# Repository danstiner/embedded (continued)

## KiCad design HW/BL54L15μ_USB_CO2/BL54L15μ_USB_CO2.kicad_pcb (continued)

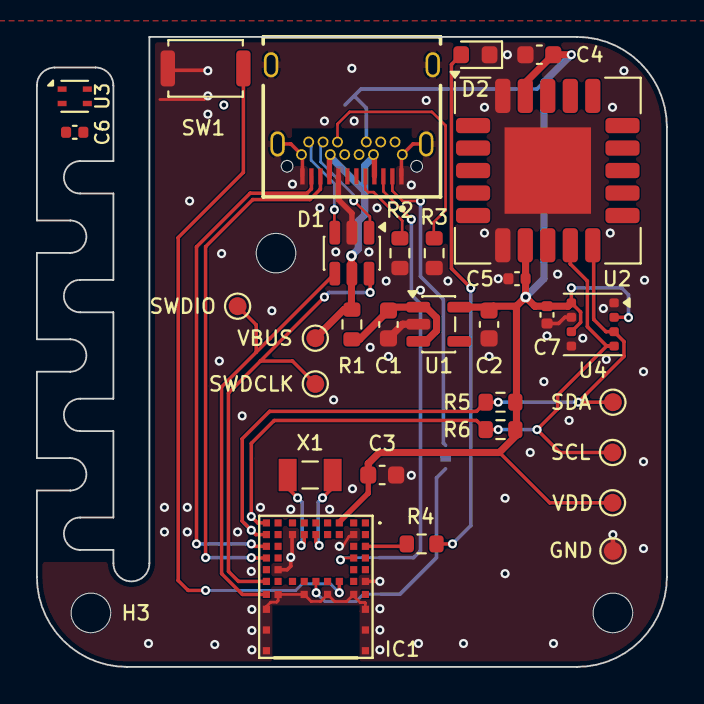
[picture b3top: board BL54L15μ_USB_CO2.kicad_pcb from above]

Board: 2 copper layers, 35.0 x 35.0 mm, 34 parts (1 on the bottom side), 22 nets.

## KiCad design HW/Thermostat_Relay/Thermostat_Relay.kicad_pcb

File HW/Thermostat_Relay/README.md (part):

# Thermostat relay board

## 1. Scope

Control board for two 24 VAC HVAC relays that can be driven by ESP32 GPIO pins. Compatible with
any typical single-stage gas furnace. Heat pumps are out of scope, they require additional
relay channels. Powering the ESP32 is also out of scope.

## 2. Background

Furnaces take mains power and step it down to 24 VAC. This is supplied on the R wire to a thermostat,
which can close the circuit with the W return wire to call for heat. In a modern furnace this is an
input to a digital control board and only draws a few milliamps. In older furnaces this directly
drives a relay coil and can draw an ampere or more of current.

## 3. Requirements

| ID   | Requirement                                                                                 |
| ---- | ------------------------------------------------------------------------------------------- |
| R-1  | Switch two independent circuits, R–W and R–G, each from one 3.3 V GPIO; high = closed       |
| R-2  | A circuit is open when its input is low or floating, or the MCU is off, in reset or booting |
| R-3  | Carry 1 A RMS continuously per circuit at 50 °C, and switch loads as small as 1 mA          |
| R-4  | Withstand 45 V peak (Class 2 transformer limit: 30 V RMS open-circuit, 42.4 V peak)         |
| R-5  | Survive switching off a 1 A inductive load                                                  |
| R-6  | Leak less than 100 µA through an open circuit                                               |
| R-7  | Galvanically isolate the MCU from the 24 VAC side                                           |
| R-8  | Draw no more than 10 mA per closed circuit from the MCU                                     |
| R-9  | Interrupt a short on the field wiring without damage to the wiring                          |
| R-10 | Surface-mount parts that can be reflowed on a hot plate; through-hole connectors            |

Notes
- 1 A is the load current TI's 24 VAC thermostat relay reference design (TIDA-010085) is
  specified for, and more than half of what a 40 VA Class 2 transformer can supply (1.7 A)
- 50 °C is a conservative ambient
- 30 V RMS maximum for thermostat circuits follows from them being Class 2 under UL 5085-3

## 4. Design trades

### 4.1 24 VAC switch

|                          | Relay    | **PhotoMOS** | Driver + FETs | TPSI8830    | TRIAC       |
| ------------------------ | -------- | ------------ | ------------- | ----------- | ----------- |
| Hold current (R-8)       | 70–90 mA | 5–10 mA      | ~5 mA         | ~5 mA       | ~10 mA      |
| 1 mA load (R-3)          | marginal | ✓            | ✓             | ✓           | ✗           |
| Leakage (R-6)            | ✓        | ✓            | ✓             | ✓           | ✗ (snubber) |
| Parts per channel        | 4        | 4            | ~10           | 3–4         | 5+          |
| Available to buy         | ✓        | ✓            | ✓             | ✗ (preview) | ✓           |
| Short-circuit protection | rugged   | none         | possible      | built in    | none        |

**Chosen: PhotoMOS.** An LED inside the package lights a photovoltaic cell that turns on two
back-to-back MOSFETs. It meets every requirement with only four parts per channel, making it easy
to use for bringing up a v1 board. A separate fuse is added for short-circuit protection.
Downsides of PhotoMOS are slightly higher cost and LED aging.

TI's reference designs for 24 VAC thermostat switching (section 10) both use discrete MOSFET pairs
with a separate isolated gate drive. This is likely a lower cost design at scale production,
using either small transformers or capacitive isolation instead of optocouplers. It also enables
microsecond switching for power-stealing, adding current-sensing circuitry, and the ability
to share one isolated supply across all channels. None of these are relevant to a v1 prototype.

TI's upcoming TPSI8830 is worth watching: it integrates a capacitively isolated driver with
back-to-back MOSFETs and overcurrent protection into a single package with 30 mΩ on resistance.

### 4.2 Furnace terminal block

Thermostat wire is nominally 18 AWG solid, connected to either screw terminals or screwless
spring terminals.

|                    | **2601-1103**        | 805-303             | 2060-453             | MKDS 1,5/3-5,08     |
| ------------------ | -------------------- | ------------------- | -------------------- | ------------------- |
| Release            | lever                | push-button         | small push-button    | screw               |
| Solid wire         | 26–14 AWG            | 24–16 AWG           | 24–18 AWG            | 26–14 AWG           |
| Pitch              | 3.5 mm               | 3.5 mm              | 4 mm                 | 5.08 mm             |
| Width × depth      | 13.0 × 15.7 mm       | 12.0 × 13.6 mm      | 11.9 × 13.1 mm       | 15.2 × 9.8 mm       |
| Height above board | about 16 mm          | 10.5 mm             | 4.5 mm               | 13.8 mm             |
| Mounting           | THT, 2 pins per pole | THT, 1 pin per pole | SMD, 2 pads per pole | THT, 1 pin per pole |

**Chosen: 2601-1103.** For prototyping we choose screwless spring terminals. Solid wire can be
pushed in by hand, and released by hand with a small lever. The 805-303 is a close alternative.
The 2060-453 has a lower profile, but release is a small button that may require a tool, and
18 AWG is the top of its range. Screw terminals have a wider pitch and require a screwdriver,
but they are typically cheaper if that becomes a driving concern.

## 5. Circuit

Two channels share the R input, each with its own fuse. Only the heat channel is shown. The
fan channel is the same except that its fuse is on pin 6 of the switch and G on pin 4; the
switch is symmetric, so this only simplifies the layout.

```
 logic side (3.3 V, USB ground) :        furnace side (24 VAC, floating)
                                :
 W_EN    o--+--[R1 220Ω]---+    :    +------+------------- o W
            |            1 | U1 :    | 6    |
         [R2 10k]        [LED]~~:~~[FETs]  [D1 TVS]
            |            2 |    :    | 4    |
 GND     o--+--------------+    :    +------+---[F1 2A]--- o R
```

### 5.1 Switch: Toshiba TLP3109A (U1)

| Datasheet value                 |                               | Requirement     |
| ------------------------------- | ----------------------------- | --------------- |
| Off-state voltage               | 100 V max                     | 45 V peak (R-4) |
| On-state current, AC connection | 3 A at 25 °C, 2.25 A at 50 °C | 1 A (R-3)       |
| On-resistance                   | 50 mΩ typ, 65 mΩ max          | –               |
| LED trigger current             | 3 mA max                      | see 5.2         |
| Off-state leakage, capacitance  | 1 µA max, 460 pF              | see 5.7         |
| Isolation                       | 1500 V RMS                    | galvanic (R-7)  |
| Pulse current                   | 9 A for 100 ms                | see 5.6         |

- Pins 4 and 6 (the two drains) are the switch; pin 5 (common source) is left open. That
  puts the two MOSFETs in series back to back, which is what lets the part block and
  conduct both polarities of AC.
- Heat: at 1 A and the maximum 65 mΩ the switch generates about 0.07 W of heat
- 100 V off-state max was chosen to have margin to clamp surges over the expected 42.4 V peak
  Class 2 transformer output, similar to TI reference design TIDA-010085.

Parts considered (DigiKey, 2026-11-12, quantity 1):

| Part         | Rating       | At 50 °C | R_on max | Isolation | Price           | Outcome     |
| ------------ | ------------ | -------- | -------- | --------- | --------------- | ----------- |
| **TLP3109A** | 100 V, 3 A   | 2.25 A   | 65 mΩ    | 1500 V    | $4.14, in stock | chosen      |
| TLP3546A     | 100 V, 3.5 A | 2.6 A    | 80 mΩ    | 2500 V    | $4.11, no stock | unavailable |

### 5.2 LED resistor: 220 Ω (R1)

The TLP3109A datasheet recommends 5 to 25 mA. `I = (V_GPIO − V_LED) / R`:

| Case            | V_GPIO | V_LED  | I      |
| --------------- | ------ | ------ | ------ |
| Worst-case low  | 3.0 V  | 1.80 V | 5.4 mA |
| Nominal         | 3.3 V  | 1.65 V | 7.5 mA |
| Worst-case high | 3.47 V | 1.50 V | 9.0 mA |

### 5.3 Optional pull-down: 10 kΩ (R2)

Optional pull-down to hold the LED input at ~0 V when not being driven (R-2). Overrides the
pull-up glitch during boot that some ESP32 pins exhibit. Optional because the TLP3109A is
guaranteed off below 0.1 mA of LED current, and a 45 kΩ pull-up supplies only about 0.05 mA.
Cannot override a pin that actively drives high during boot, those high-level glitch pins
should be avoided.

### 5.4 Optional indicator: 4.7 kΩ and a red LED

One LED per channel, from the control input to ground, lit while the ESP32 commands the
channel closed. At 4.7 kΩ it draws about 0.3 mA, 0.4 mA worst case. With the pull-down and
indicator both fitted, a closed channel draws at most 9.0 + 0.35 + 0.4 = 9.7 mA (R-8).

### 5.5 Clamp: Bidirectional TVS (D1)

When the switch opens on a relay coil or gas valve, the coil's inductance creates a voltage
spike across the switch. A bidirectional TVS across the switch limits that voltage (R-5)
to prevent damage to the switch.

|                     | SMBJ48CA       | Requirement                       |
| ------------------- | -------------- | --------------------------------- |
| Reverse stand off   | 48 V           | ≥ 45 V peak (R-4)                 |
| Max clamp           | 77.4 V @ 7.8 A | ≤ 80 V (switch's recommended max) |
| Max reverse leakage | 1 µA           | < 100 µA total leakage (R-6)      |

An RC snubber is ruled out by R-6: a typical 100 nF passes about 1.1 mA at 60 Hz with the
switch open, which could trigger a phantom call for heat on a modern furnace control board.

### 5.6 Fuses: 2 A very fast-acting, one per channel (F1)

Each fuse opens if its circuit is shorted while that channel is closed (R-9): a
shorted relay coil, or the wire touching the transformer's return or grounded metal. That
protects the cable, the transformer and, for moderate fault currents, the switch. One fuse
per channel means a fault on the fan wire cannot take out the heat, and each fuse is sized
for one load, not the sum.

| Littelfuse 0466002.NR | Datasheet                            | Requirement                       |
| --------------------- | ------------------------------------ | --------------------------------- |
| Voltage rating        | 63 VAC                               | 30 V RMS (R-4)                    |
| Interrupting rating   | 50 A at 63 VAC                       | transformer short-circuit current |
| Continuous current    | 1.5 A at 25 °C, about 1.3 A at 50 °C | 1 A (R-3)                         |
| Opens at 200 % (4 A)  | within 5 s                           | –                                 |
| Opens at 300 % (6 A)  | within 0.2 s                         | –                                 |
| Melting I²t           | 0.23 A²s                             | below the switch's 8 A²s          |
| Cold resistance       | 30 mΩ                                | –                                 |

- Sizing: Littelfuse's guidance is to run a fuse at no more than 75 % of its rating at
  25 °C, which gives 1.5 A. The datasheet rerates a further 20 % at 70 °C; interpolating,
  about 11 % at 50 °C gives 1.3 A. That leaves about 30 % margin over a 1 A load. Relay
  coil inrush against the low melting I²t is unverified (section 9).
- Compared with others: TI recommends the same 2 A fast fuse for its 1 A design
  (TIDA-010085) and tested with the 1.5 A part of this series. Furnace control boards
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
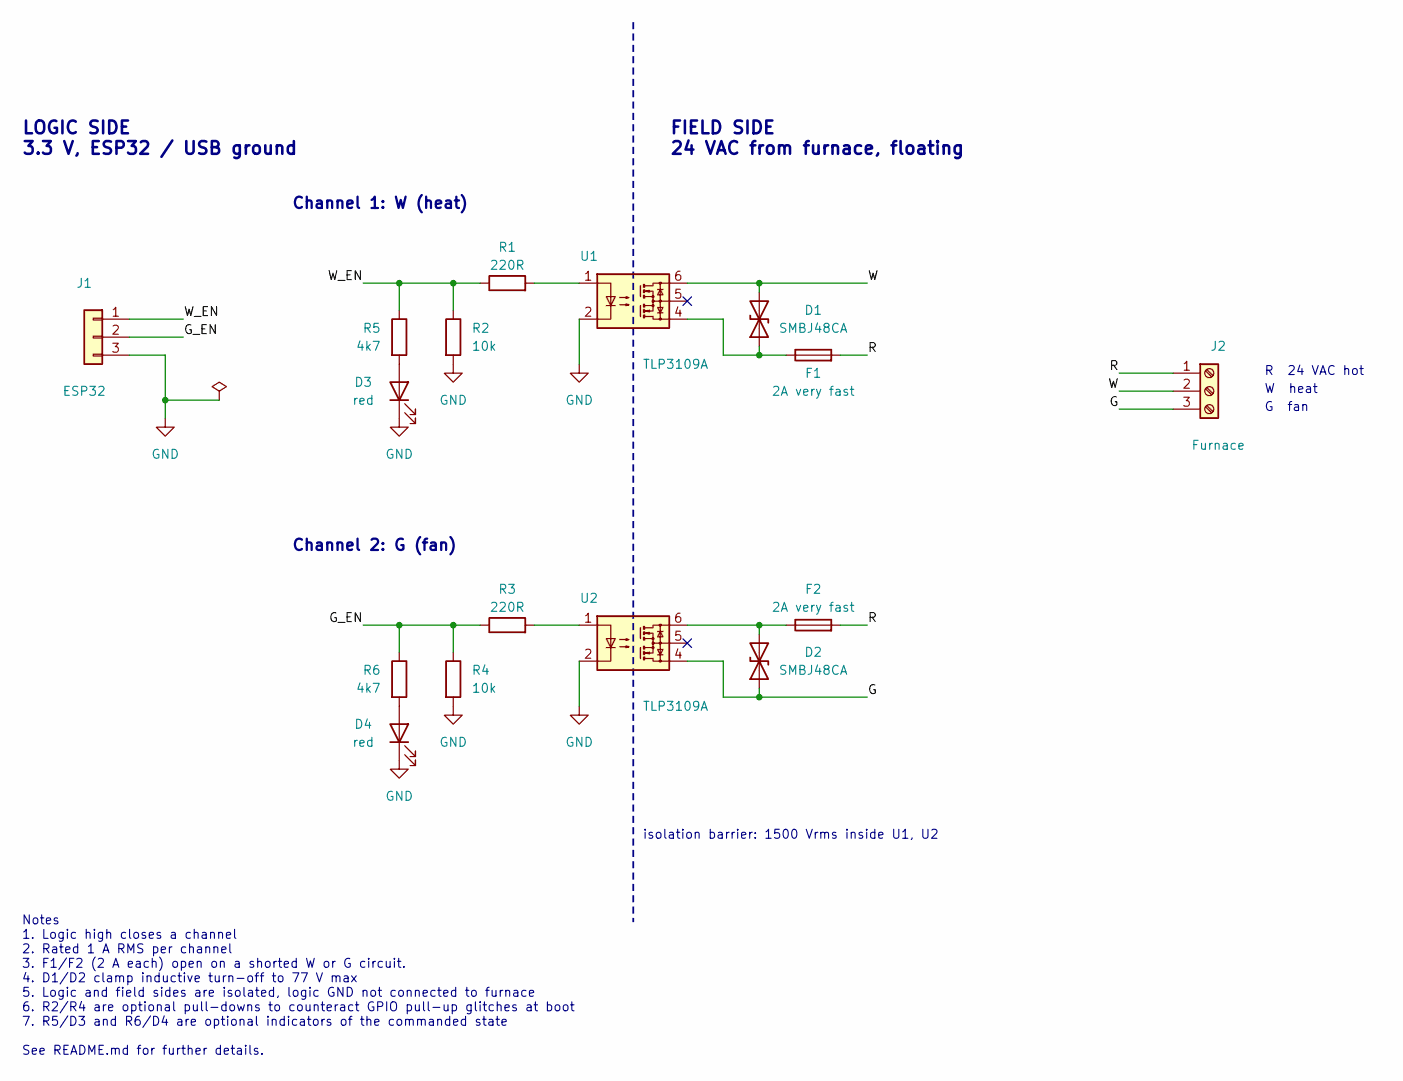
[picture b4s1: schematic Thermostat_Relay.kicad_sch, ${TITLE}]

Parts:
D1, D2: SMBJ48CA; D_SMB_Handsoldering; MPN SMBJ48CA
D3, D4: red; LED_0603_1608Metric_Pad1.05x0.95mm_HandSolder; MPN 150060SS75000
F1, F2: 2A very fast; Fuse_1206_3216Metric_Pad1.42x1.75mm_HandSolder; MPN 0466002.NR
J1: ESP32; PinHeader_1x03_P2.54mm_Vertical
J2: Furnace; TerminalBlock_WAGO_2601-1103_1x03_P3.50mm_Horizontal; MPN 2601-1103
R1, R3: 220R; R_0603_1608Metric_Pad0.98x0.95mm_HandSolder; Tolerance 1%; MPN RC0603FR-07220RL
R2, R4: 10k; R_0603_1608Metric_Pad0.98x0.95mm_HandSolder; MPN RC0603FR-0710KL
R5, R6: 4k7; R_0603_1608Metric_Pad0.98x0.95mm_HandSolder; MPN RC0603FR-074K7L
U1, U2: TLP3109A; 2p54SOP6_TOS-M; MPN TLP3109A(TP,F

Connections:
/G: D2.1 (A1), J2.3, U2.4
/G_EN: J1.2, R3.1, R4.1, R6.1
/R: F1.2, F2.2, J2.1
/W: D1.2 (A2), J2.2, U1.6
/W_EN: J1.1, R1.1, R2.1, R5.1
GND: D3.1 (K), D4.1 (K), J1.3, R2.2, R4.2, U1.2, U2.2
unnamed: D1.1 (A1), F1.1, U1.4
unnamed: D2.2 (A2), F2.1, U2.6
unnamed: D3.2 (A), R5.2
unnamed: D4.2 (A), R6.2
unnamed: R1.2, U1.1
unnamed: R3.2, U2.1

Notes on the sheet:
FIELD SIDE 24 VAC from furnace, floating
R 24 VAC hot
LOGIC SIDE 3.3 V, ESP32 / USB ground
Channel 2: G (fan)
W heat
Channel 1: W (heat)
Notes 1. Logic high closes a channel 2. Rated 1 A RMS per channel 3. F1/F2 (2 A each) open on a shorted W or G circuit. 4. D1/D2 clamp inductive turn-off to 77 V max 5. Logic and field sides are isolated, logic GND not connected to furnace 6. R2/R4 are optional pull-downs to counteract GPIO pull-up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
G fan
isolation barrier: 1500 Vrms inside U1, U2

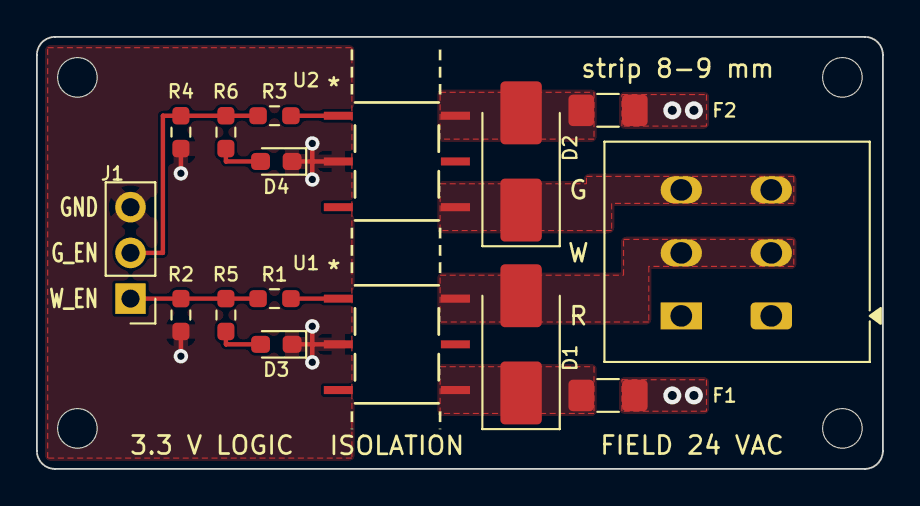
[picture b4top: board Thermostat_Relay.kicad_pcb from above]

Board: 2 copper layers, 47.0 x 24.0 mm, 20 parts (0 on the bottom side), 12 nets.

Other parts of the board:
H1, H2, H3, H4: MountingHole_2.2mm_M2

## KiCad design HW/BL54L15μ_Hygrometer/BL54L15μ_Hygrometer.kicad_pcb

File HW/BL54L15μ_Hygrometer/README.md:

+-----------+-----+----------------------+-----------------------------------------+--------------------------------------------------------------------------------------+
| Reference | Qty | Value                | Part Number                             | Footprint                                                                            |
+-----------+-----+----------------------+-----------------------------------------+--------------------------------------------------------------------------------------+
| BT1       | 1   | CR2 Battery          | 1011                                    | 1011:BAT_1011                                                                        |
| BZ1       | 1   | AST0827MW-03BTRQ     | AST0827MW-03BTRQ                        | AST0827MW-03BTRQ:AST0827MW-03BTRQ_MAL                                                |
| C1        | 1   | 100nF                | GRM155R61A104KA01J                      | Capacitor_SMD:C_0402_1005Metric                                                      |
| C2,C3     | 2   | 10μF                 | CL10A106KP8NNNC                         | Capacitor_SMD:C_0603_1608Metric                                                      |
| D1,D2     | 2   | 5V TVS               | TPD1E10B06DPYR                          | Diode_SMD:D_0402_1005Metric                                                          |
| D3        | 1   | MBR0520L             | MBR0520LT3G                             | Diode_SMD:D_SOD-123                                                                  |
| IC1       | 1   | nrf54L 453-00223R    | 453-00223R                              | 453-00223R:45300223R                                                                 |
| J1        | 1   | Conn_ARM_JTAG_SWD_10 | 3220-10-0300-00                         | Connector_PinHeader_1.27mm:PinHeader_2x05_P1.27mm_Vertical_SMD                       |
| P1,P2     | 2   | 6mmMetalDome         | Triangle 6mm - 0.8mm feet               | MetalDomeSwitch:TriangleDome_Diameter6mm                                             |
| Q1        | 1   | AOSS32136C           | AOSS32136C                              | Package_TO_SOT_SMD:SOT-23-3                                                          |
| R1,R2     | 2   | 10kΩ                 | RC0402FR-0710KL                         | Resistor_SMD:R_0402_1005Metric                                                       |
| R3,R7     | 2   | 1MΩ                  | RC0402FR-071ML                          | Resistor_SMD:R_0402_1005Metric                                                       |
| U1        | 1   | SHT4x                | SHT45-AD1F-R2                           | Sensor_Humidity:Sensirion_DFN-4_1.5x1.5mm_P0.8mm_SHT4x_NoCentralPad                  |
| X1        | 1   | 32.768 kHz           | CM7V-T1A-LOW-ESR-32.768KHZ-9PF-20-TA-QC | CM7V_T1A_LOW_ESR_32_768KHZ_9PF_20_TA_QC:XTAL_CM7V-T1A-LOW-ESR-32.768KHZ-9PF-20-TA-QC |
+-----------+-----+----------------------+-----------------------------------------+--------------------------------------------------------------------------------------+

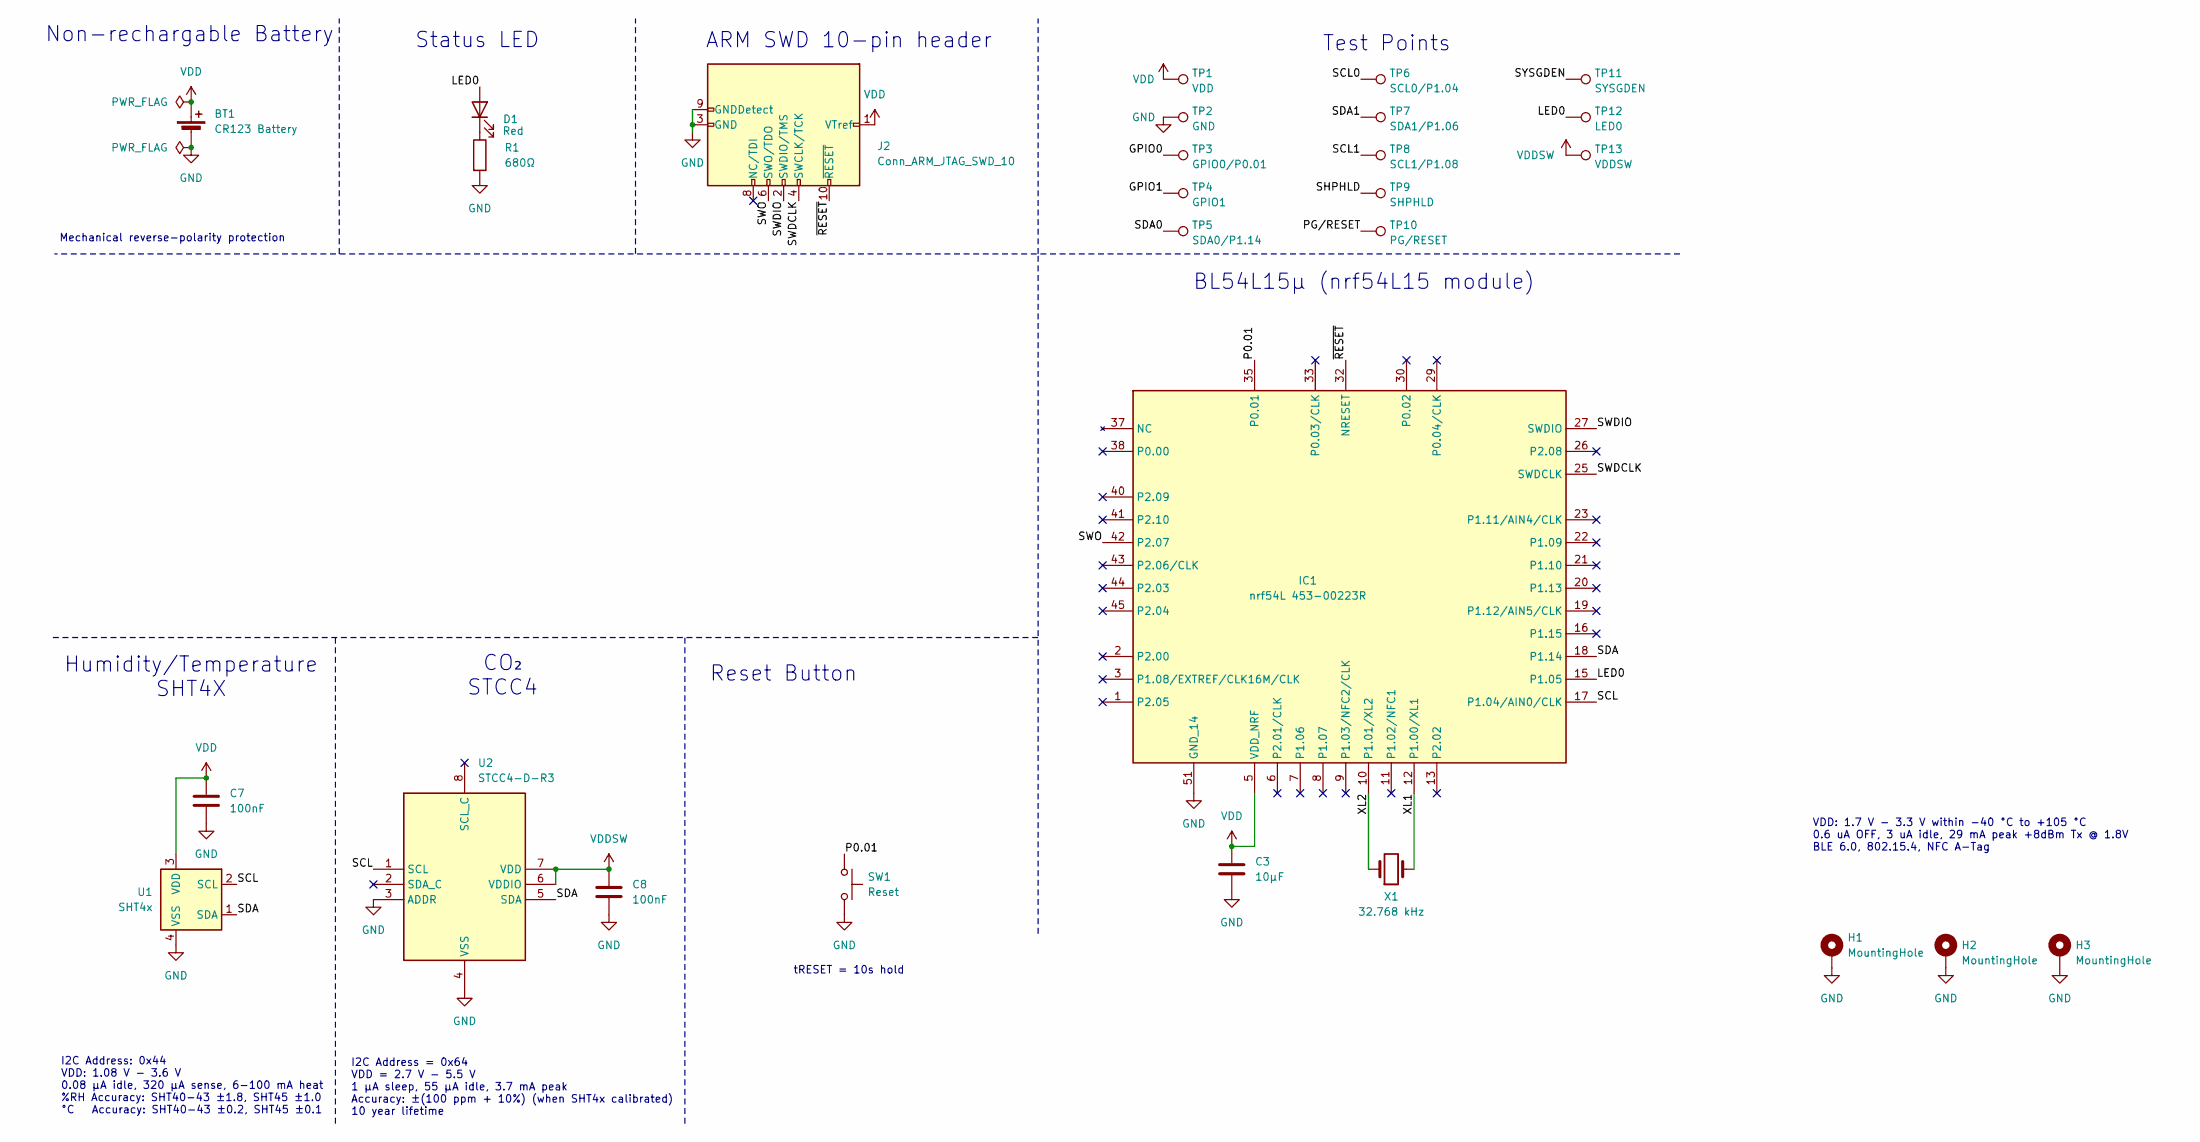
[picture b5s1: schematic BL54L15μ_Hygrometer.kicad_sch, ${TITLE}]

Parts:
BT1: CR123 Battery; BAT_1011; Part Number 1011
C3: 10μF; C_0603_1608Metric; Part Number CL10A106KP8NNNC
C7, C8: 100nF; C_0402_1005Metric; Part Number GRM155R61A104KA01J
D1: PWRLED; LED_0603_1608Metric; Part Number 150060SS75000; Digikey Part Number 732-4979-1-ND
H1, H2, H3: MountingHole; MountingHole_2.2mm_M2_Pad
IC1: nrf54L 453-00223R; 45300223R; Part Number 453-00223R; Digikey Part Number 776-453-00223RCT-ND
J2: Conn_ARM_JTAG_SWD_10; PinHeader_2x05_P1.27mm_Vertical_SMD; Digikey Part Number 1528-752-ND
R1: 680Ω; R_0603_1608Metric; Part Number RC0603JR-13680RL
SW1: Reset; SW_Push_SPST_NO_Alps_SKRK; Part Number SKRKAHE020; Digikey Part Number 4809-SKRKAHE020CT-ND
TP1: VDD; TestPoint_Pad_D1.0mm
TP2: GND; TestPoint_Pad_1.0x1.0mm
TP3: GPIO0/P0.01; TestPoint_Pad_D1.0mm
TP4: GPIO1; TestPoint_Pad_D1.0mm
TP5: SDA0/P1.14; TestPoint_Pad_D1.0mm
TP6: SCL0/P1.04; TestPoint_Pad_D1.0mm
TP7: SDA1/P1.06; TestPoint_Pad_D1.0mm
TP8: SCL1/P1.08; TestPoint_Pad_D1.0mm
TP9: SHPHLD; TestPoint_Pad_D1.0mm
TP10: PG/RESET; TestPoint_Pad_D1.0mm
TP11: SYSGDEN; TestPoint_Pad_D1.0mm
TP12: LED0; TestPoint_Pad_D1.0mm
TP13: VDDSW; TestPoint_Pad_D1.0mm
U1: SHT4x; Sensirion_DFN-4_1.5x1.5mm_P0.8mm_SHT4x_NoCentralPad; Part Number SHT45-AD1F-R2
U2: STCC4-D-R3; STCC4DR3; Part Number STCC4-D-R3; Digikey Part Number 1649-STCC4-D-R3CT-ND
X1: 32.768 kHz; XTAL_CM7V-T1A-LOW-ESR-32.768KHZ-9PF-20-TA-QC; Part Number CM7V-T1A-LOW-ESR-32.768KHZ-9PF-20-TA-QC; Digikey Part Number 2195-CM7VT1ALOWESR32.768KHZ9PF20TAQCCT-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

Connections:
/GPIO0: TP3.1 (1_1)
/GPIO1: TP4.1 (1_1)
/LED0: D1.2 (A), IC1.15 (P1.05), TP12.1 (1_1)
/P0.01: IC1.35 (P0.01), SW1.1
/PG/RESET: TP10.1 (1_1)
/SCL: IC1.17 (P1.04/AIN0/CLK), U1.2 (SCL), U2.1 (SCL)
/SCL0: TP6.1 (1_1)
/SCL1: TP8.1 (1_1)
/SDA: IC1.18 (P1.14), U1.1 (SDA), U2.5 (SDA)
/SDA0: TP5.1 (1_1)
/SDA1: TP7.1 (1_1)
/SHPHLD: TP9.1 (1_1)
/SWDCLK: IC1.25 (SWDCLK), J2.4 (SWCLK/TCK)
/SWDIO: IC1.27 (SWDIO), J2.2 (SWDIO/TMS)
/SWO: IC1.42 (P2.07), J2.6 (SWO/TDO)
/SYSGDEN: TP11.1 (1_1)
/XL1: IC1.12 (P1.00/XL1), X1.2
/XL2: IC1.10 (P1.01/XL2), X1.1
/~RESET: IC1.32 (NRESET), J2.10 (~RESET)
GND: BT1.2 (-), C3.2, C7.2, C8.2, H1.1 (1_1), H2.1 (1_1), H3.1 (1_1), IC1.4 (GND_1), IC1.14 (GND_2), IC1.24 (GND_3), IC1.28 (GND_4), IC1.31 (GND_5), IC1.34 (GND_6), IC1.36 (GND_7), IC1.39 (GND_8), IC1.46 (GND_9), IC1.47 (GND_10), IC1.48 (GND_11), IC1.49 (GND_12), IC1.50 (GND_13), IC1.51 (GND_14), J2.3 (GND), J2.5 (GND), J2.9 (GNDDetect), R1.2, SW1.2, TP2.1 (1_1), U1.4 (VSS), U2.3 (ADDR), U2.4 (VSS)
unnamed: D1.1 (K), R1.1
VDD: BT1.1 (+), C3.1, C7.1, IC1.5 (VDD_NRF), J2.1 (VTref), TP1.1 (1_1), U1.3 (VDD)
VDDSW: C8.1, TP13.1 (1_1), U2.6 (VDDIO), U2.7 (VDD)

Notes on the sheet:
Mechanical reverse-polarity protection
VDD: 1.7 V - 3.3 V within -40 °C to +105 °C 0.6 uA OFF, 3 uA idle, 29 mA peak +8dBm Tx @ 1.8V BLE 6.0, 802.15.4, NFC A-Tag
Humidity/Temperature SHT4X
CO₂ STCC4
tRESET = 10s hold
I2C Address = 0x64 VDD = 2.7 V - 5.5 V 1 μA sleep, 55 μA idle, 3.7 mA peak Accuracy: ±(100 ppm + 10%) (when SHT4x calibrated) 10 year lifetime
Test Points
Non-rechargable Battery
BL54L15μ (nrf54L15 module)
Status LED
I2C Address: 0x44 VDD: 1.08 V - 3.6 V 0.08 μA idle, 320 μA sense, 6-100 mA heat %RH Accuracy: SHT40-43 ±1.8, SHT45 ±1.0 °C Accuracy: SHT40-43 ±0.2, SHT45 ±0.1
ARM SWD 10-pin header
Reset Button

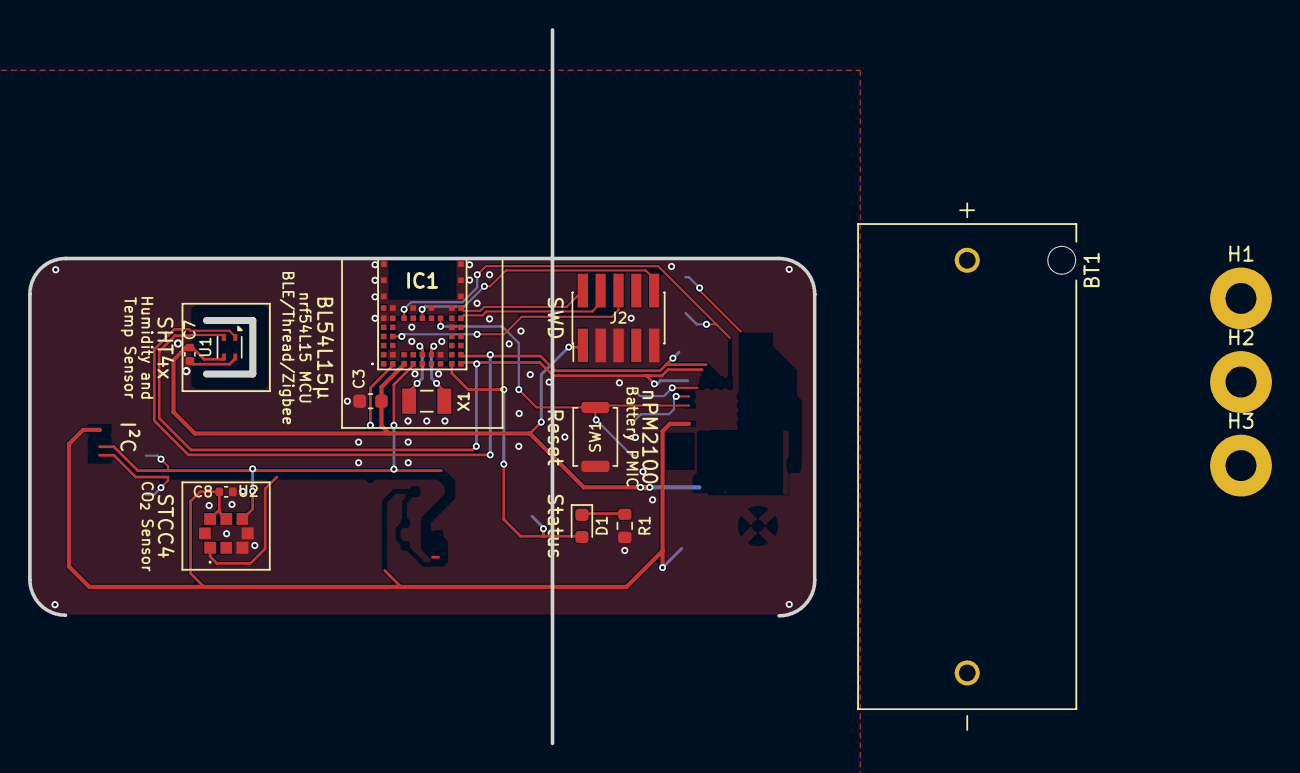
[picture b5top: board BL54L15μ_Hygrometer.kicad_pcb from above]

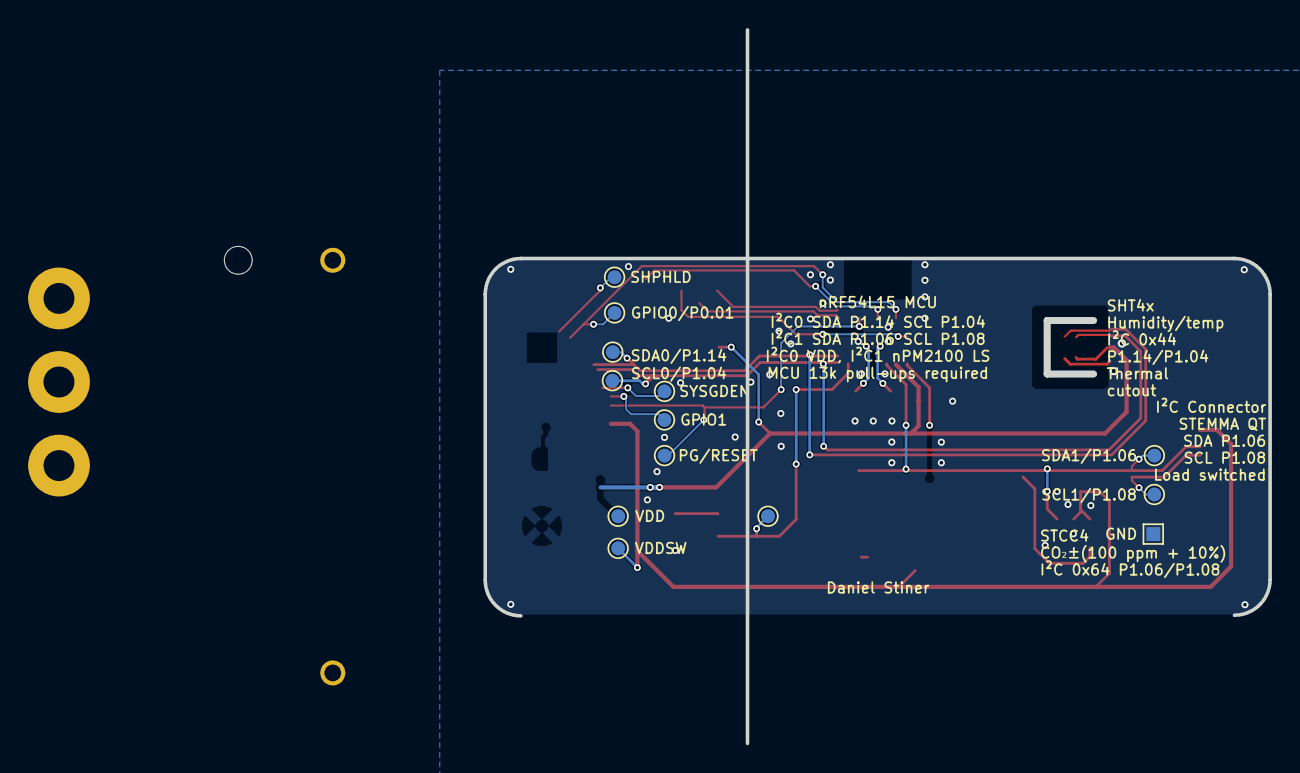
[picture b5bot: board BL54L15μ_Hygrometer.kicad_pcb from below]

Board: 2 copper layers, 55.9 x 50.8 mm, 28 parts (13 on the bottom side), 14 nets.

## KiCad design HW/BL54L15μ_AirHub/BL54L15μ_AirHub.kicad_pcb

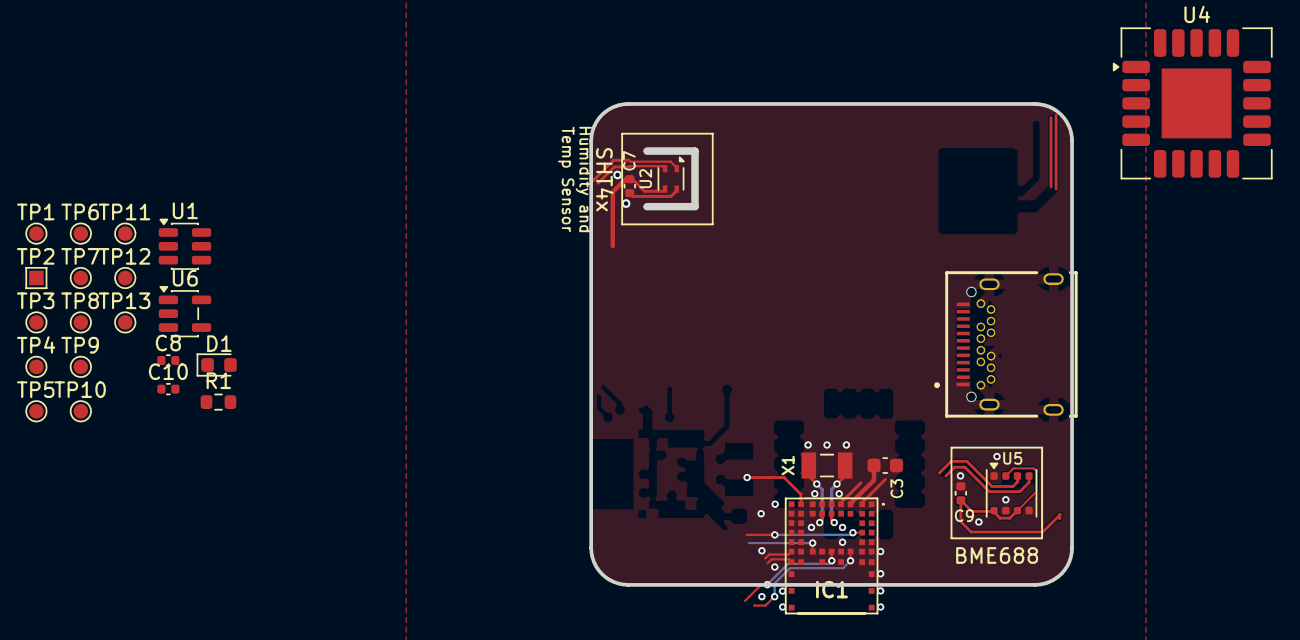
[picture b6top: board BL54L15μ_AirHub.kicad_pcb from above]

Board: 2 copper layers, 33.0 x 33.0 mm, 28 parts (0 on the bottom side), 20 nets.

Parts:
C3: 10μF; C_0603_1608Metric
C7, C8, C9, C10: 100nF; C_0402_1005Metric
D1: PWRLED; LED_0603_1608Metric
IC1: nrf54L 453-00223R; 45300223R
J3: USB_C_Receptacle; GCT_USB4056-03-A_REVA2
R1: 100Ω; R_0603_1608Metric
TP1: VDD; TestPoint_Pad_D1.0mm
TP2: GND; TestPoint_Pad_1.0x1.0mm
TP3: GPIO0/P0.01; TestPoint_Pad_D1.0mm
TP4: GPIO1; TestPoint_Pad_D1.0mm
TP5: SDA0/P1.14; TestPoint_Pad_D1.0mm
TP6: SCL0/P1.04; TestPoint_Pad_D1.0mm
TP7: SDA1/P1.06; TestPoint_Pad_D1.0mm
TP8: SCL1/P1.08; TestPoint_Pad_D1.0mm
TP9: SHPHLD; TestPoint_Pad_D1.0mm
TP10: PG/RESET; TestPoint_Pad_D1.0mm
TP11: SYSGDEN; TestPoint_Pad_D1.0mm
TP12: LED0; TestPoint_Pad_D1.0mm
TP13: VDDSW; TestPoint_Pad_D1.0mm
U1: USBLC6-2SC6; SOT-23-6
U2: SHT4x; Sensirion_DFN-4_1.5x1.5mm_P0.8mm_SHT4x_NoCentralPad
U4: SCD4X; Sensirion_SCD4x-1EP_10.1x10.1mm_P1.25mm_EP4.8x4.8mm
U5: BME688; Bosch_LGA-8_3x3mm_P0.8mm_ClockwisePinNumbering
U6: AP2112K-3.3; SOT-23-5
X1: 32.768 kHz; XTAL_CM7V-T1A-LOW-ESR-32.768KHZ-9PF-20-TA-QC

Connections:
/GPIO0: IC1.35 (P0.01), TP3.1 (1_1)
/LED0: D1.2 (A), IC1.15 (P1.05), TP12.1 (1_1)
/PG/RESET: IC1.29 (P0.04/CLK), TP10.1 (1_1)
/SCL: U2.2 (SCL), U4.9 (SCL), U5.4 (SCK)
/SCL0: IC1.17 (P1.04/AIN0/CLK), TP6.1 (1_1)
/SCL1: IC1.3 (P1.08/EXTREF/CLK16M/CLK), TP8.1 (1_1)
/SDA: U2.1 (SDA), U4.10 (SDA), U5.3 (SDI)
/SDA0: IC1.18 (P1.14), TP5.1 (1_1)
/SDA1: IC1.7 (P1.06), TP7.1 (1_1)
/SWDCLK: IC1.25 (SWDCLK), U1.6 (I/O1)
/SWDIO: IC1.27 (SWDIO), U1.4 (I/O2)
/XL1: IC1.12 (P1.00/XL1), X1.2
/XL2: IC1.10 (P1.01/XL2), X1.1
/~RESET: IC1.32 (NRESET), J3.B2 (TX2+)
GND: C3.2, C7.2, C8.2, C9.2, C10.2, IC1.4 (GND_1), IC1.14 (GND_2), IC1.24 (GND_3), IC1.28 (GND_4), IC1.31 (GND_5), IC1.34 (GND_6), IC1.36 (GND_7), IC1.39 (GND_8), IC1.46 (GND_9), IC1.47 (GND_10), IC1.48 (GND_11), IC1.49 (GND_12), IC1.50 (GND_13), IC1.51 (GND_14), J3.A1 (GND), J3.A12 (GND), J3.B1 (GND), J3.B8 (SBU2), J3.B12 (GND), J3.S1 (SHIELD), R1.2, TP2.1 (1_1), U1.2 (GND), U2.4 (VSS), U4.6 (GND), U4.20 (GND), U4.21 (GND), U5.1 (GND), U5.5 (SDO), U5.7 (GND), U6.2 (GND)
unnamed: D1.1 (K), R1.1
unnamed: J3.A2 (TX1+), U1.3 (I/O2)
unnamed: J3.A3 (TX1-), U1.1 (I/O1)
VBUS: J3.A4 (VBUS), J3.A9 (VBUS), J3.B4 (VBUS), J3.B9 (VBUS), U1.5 (VBUS), U6.1 (VIN), U6.3 (EN)
VDD: C3.1, C7.1, C8.1, C9.1, C10.1, IC1.5 (VDD_NRF), J3.A8 (SBU1), TP1.1 (1_1), U2.3 (VDD), U4.7 (VDD), U4.19 (VDD), U5.2 (CSB), U5.6 (VDDIO), U5.8 (VDD), U6.5 (VOUT)

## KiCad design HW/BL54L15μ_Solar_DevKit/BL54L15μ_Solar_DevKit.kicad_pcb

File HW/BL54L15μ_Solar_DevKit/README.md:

## BOM

+------------------+-----+--------------------+-----------------------------------------+---------------------------------------------------------------------+
|    Reference     | Qty |       Value        |               Part Number               |                              Footprint                              |
+------------------+-----+--------------------+-----------------------------------------+---------------------------------------------------------------------+
| C1,C5            |   2 | 1μF                | CL05A105KA5NQNC                         | Capacitor_SMD:C_0402_1005Metric                                     |
| C2,C4,C7,C10,C11 |   5 | 10μF               | CL10A106KP8NNNC                         | Capacitor_SMD:C_0603_1608Metric                                     |
| C3               |   1 | 10uF               | CL10A106KP8NNNC                         | Capacitor_SMD:C_0603_1608Metric                                     |
| C6               |   1 | 2.2μF              | CL05A225KP5NSNC                         | Capacitor_SMD:C_0402_1005Metric                                     |
| C8,C9            |   2 | 1μF                | CL10A105KP8NNNC                         | Capacitor_SMD:C_0603_1608Metric                                     |
| C12              |   1 | 100nF              | CL05B103KB5NNNC                         | Capacitor_SMD:C_0402_1005Metric                                     |
| D1               |   1 | PWRLED             | 150060GS75000                           | LED_SMD:LED_0603_1608Metric                                         |
| D2               |   1 | PWRLED             | 150060SS75000                           | LED_SMD:LED_0603_1608Metric                                         |
| D3               |   1 | WL-SFTW_3528_PLCC6 | 150352M173300                           | 150352M173300:WL-SFTW_3528_PLCC6                                    |
| IC1              |   1 | nrf54L 453-00223R  | 453-00223R                              | Ezurio 453-00223R:45300223R                                         |
| J1               |   1 | Conn_Qwiic_1       | BM04B-SRSS-TB                           | Connector_JST:JST_SH_BM04B-SRSS-TB_1x04-1MP_P1.00mm_Vertical        |
| J2               |   1 | USB_C_Receptacle   | USB4056-03-A                            | USB4056_03_A:GCT_USB4056-03-A_REVA2                                 |
| J3,J4            |   2 | Conn_01x12_Pin     |                                         | Connector_PinHeader_2.54mm_SilkFree:PinHeader_1x12_P2.54mm_Vertical |
| J5               |   1 | Conn_01x02         |                                         | Connector_PinHeader_2.54mm:PinHeader_1x03_P2.54mm_Vertical          |
| J6,J7            |   2 | Conn_01x02         | B2B-PH-K-S                              | Connector_JST:JST_PH_B2B-PH-K_1x02_P2.00mm_Vertical                 |
| J8               |   1 | Conn_Qwiic_2       | BM04B-SRSS-TB                           | Connector_JST:JST_SH_BM04B-SRSS-TB_1x04-1MP_P1.00mm_Vertical        |
| L1,L2            |   2 | 2.2 μH             | CIGT201610EH2R2MNE                      | CIGT201610EH2R2MNE:IND_CIGT2016_SAM                                 |
| R1               |   1 | 2kΩ                | RC0402FR-132KL                          | Resistor_SMD:R_0402_1005Metric                                      |
| R2               |   1 | 250-500 kΩ         | RC0603JR-07330KL                        | Resistor_SMD:R_0603_1608Metric                                      |
| R3               |   1 | 47 kΩ              | RC0603FR-0747KL                         | Resistor_SMD:R_0603_1608Metric                                      |
| R4               |   1 | 100Ω               | RC0603FR-07100RL                        | Resistor_SMD:R_0603_1608Metric                                      |
| SW1              |   1 | Button0            | SKRKAHE020                              | Button_Switch_SMD:SW_Push_SPST_NO_Alps_SKRK                         |
| SW2              |   1 | Reset              | SKRKAHE020                              | Button_Switch_SMD:SW_Push_SPST_NO_Alps_SKRK                         |
| U1               |   1 | NPM1304-QEAA       | NPM1304-QEAA-R7                         | Package_QFN:QFN-32-1EP_5x5mm_P0.5mm_EP3.6x3.6mm_10milThermalVias    |
| X1               |   1 | 32.768 kHz         | CM7V-T1A-LOW-ESR-32.768KHZ-9PF-20-TA-QC | Crystal:Crystal_SMD_2012-2Pin_2.0x1.2mm                             |
+------------------+-----+--------------------+-----------------------------------------+---------------------------------------------------------------------+

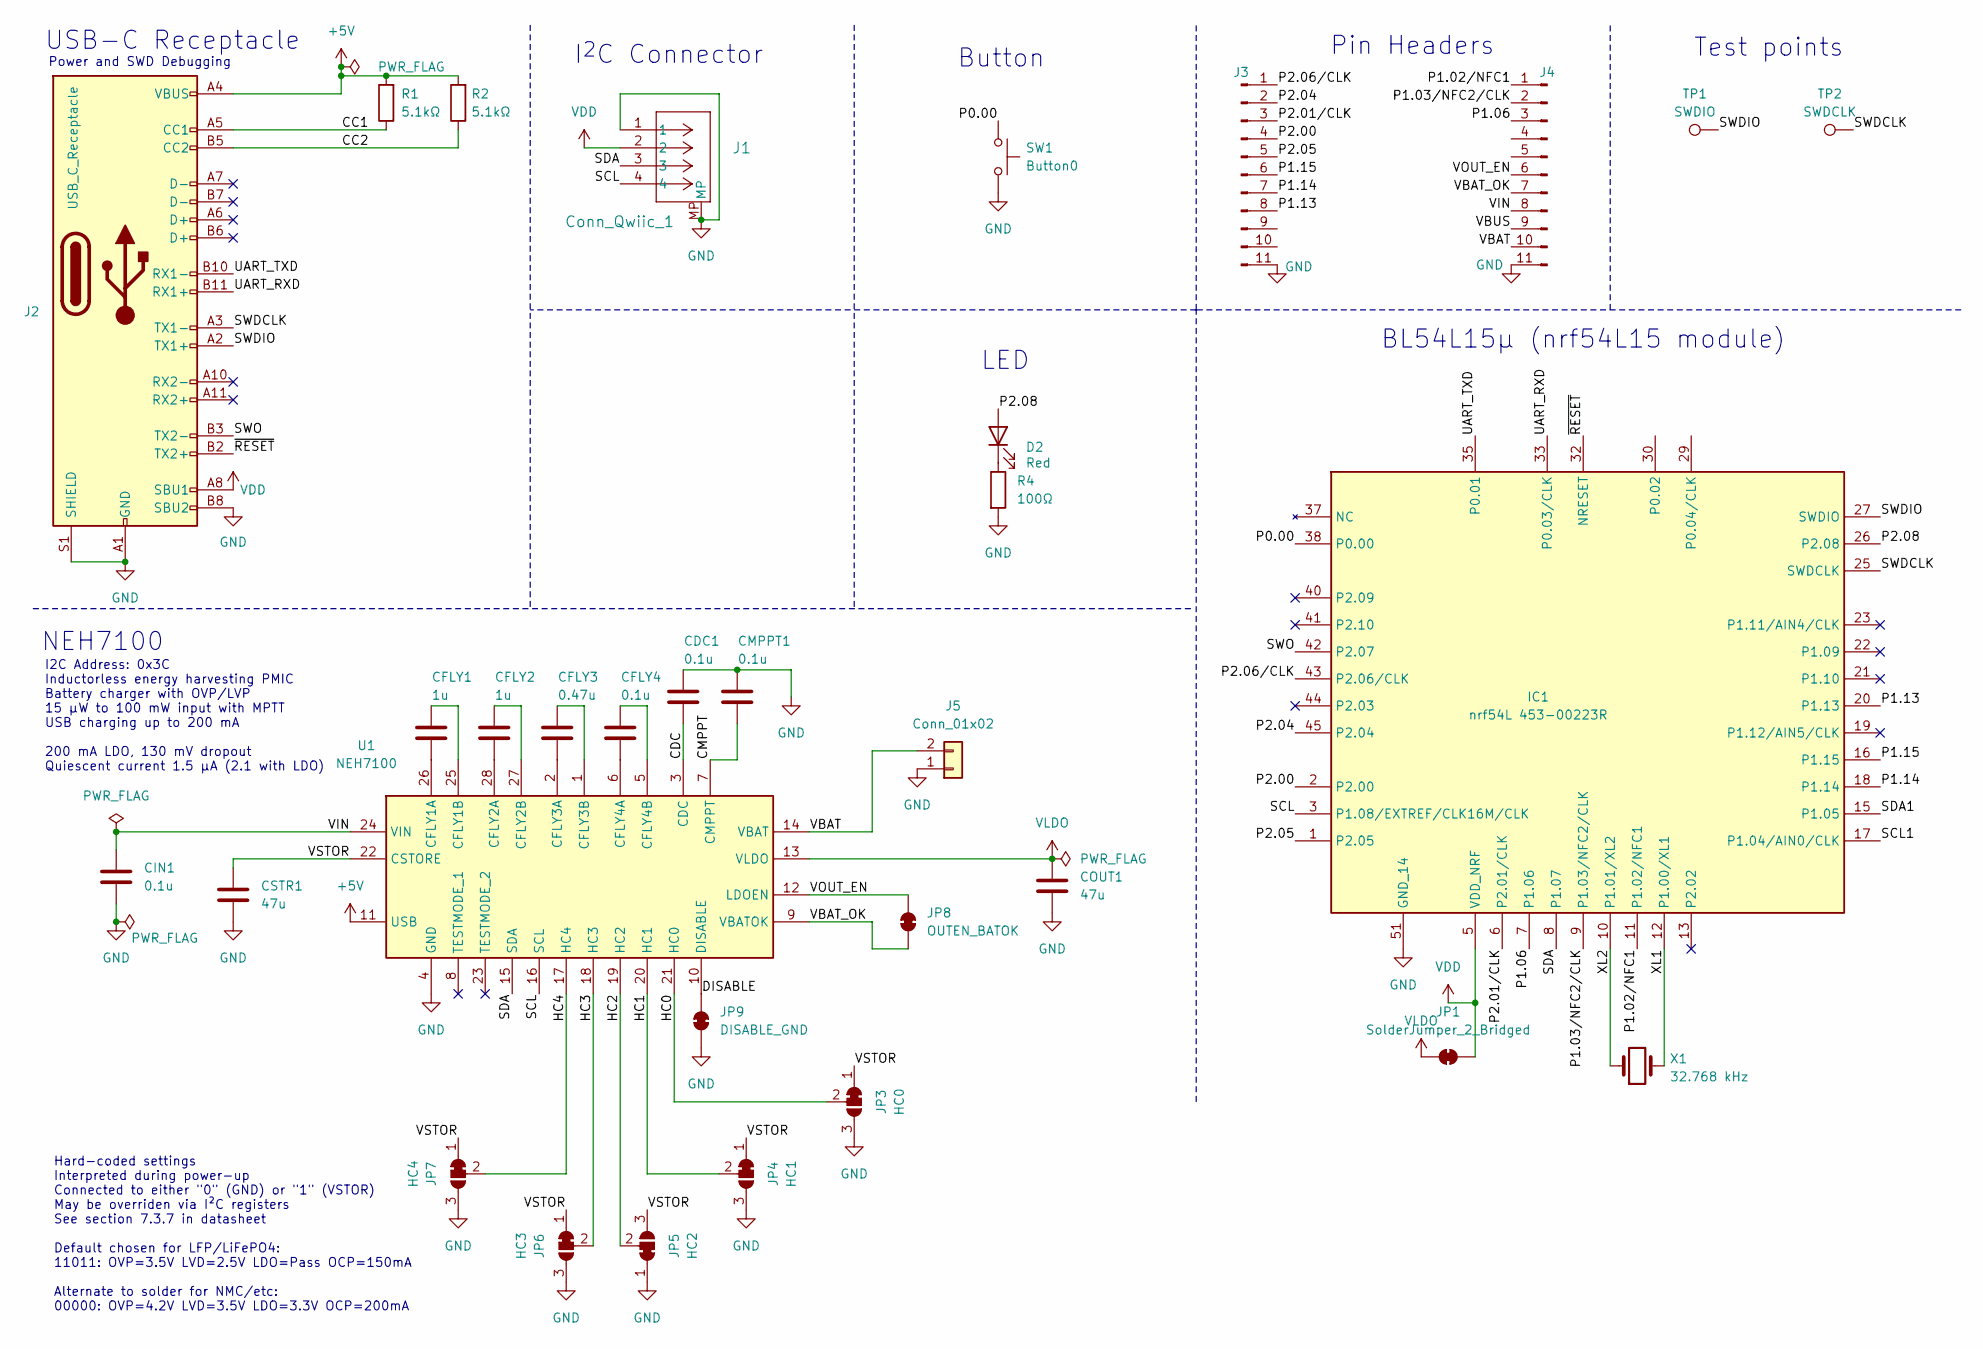
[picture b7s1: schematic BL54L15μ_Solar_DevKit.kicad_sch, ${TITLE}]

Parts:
CDC1: 0.1u; C_0402_1005Metric; Part Number GRM155R61A104KA01J
CFLY1, CFLY2: 1u; C_0402_1005Metric; Part Number GRM153R61A105ME95D
CFLY3: 0.47u; C_0402_1005Metric; Part Number GRM155R61A474KE15D
CFLY4: 0.1u; C_0402_1005Metric; Part Number GRM155R61A104KA01J
CIN1: 0.1u; C_0402_1005Metric; Part Number GRM155R61A104KA01J
CMPPT1: 0.1u; C_0402_1005Metric; Part Number GRM155R61A104KA01J
COUT1: 47u; C_0603_1608Metric; Part Number GRM188R60J476ME15D
CSTR1: 47u; C_0603_1608Metric; Part Number GRM188R60J476ME15D
D2: PWRLED; LED_0603_1608Metric; Part Number 150060SS75000
IC1: nrf54L 453-00223R; 45300223R; Part Number 453-00223R
J1: Conn_Qwiic_1; JST_SH_BM04B-SRSS-TB_1x04-1MP_P1.00mm_Vertical; Part Number BM04B-SRSS-TB
J2: USB_C_Receptacle; GCT_USB4056-03-A_REVA2; Part Number USB4056-03-A
J3, J4: Conn_01x12_Pin; PinHeader_1x11_P2.54mm_Vertical
J5: Conn_01x02; JST_PH_B2B-PH-K_1x02_P2.00mm_Vertical
JP1: SolderJumper_2_Bridged
JP3: HC0; SolderJumper-3_P1.3mm_Bridged12_RoundedPad1.0x1.5mm
JP4: HC1; SolderJumper-3_P1.3mm_Bridged12_RoundedPad1.0x1.5mm
JP5: HC2; SolderJumper-3_P1.3mm_Bridged12_RoundedPad1.0x1.5mm
JP6: HC3; SolderJumper-3_P1.3mm_Bridged12_RoundedPad1.0x1.5mm
JP7: HC4; SolderJumper-3_P1.3mm_Bridged12_RoundedPad1.0x1.5mm
JP8: OUTEN_BATOK; SolderJumper-2_P1.3mm_Bridged_RoundedPad1.0x1.5mm
JP9: DISABLE_GND; SolderJumper-2_P1.3mm_Bridged_RoundedPad1.0x1.5mm
R1, R2: 5.1kΩ
R4: 100Ω; R_0603_1608Metric; Part Number RC0603FR-07100RL
SW1: Button0; SW_Push_SPST_NO_Alps_SKRK; Part Number SKRKAHE020; Digikey Part Number 4809-SKRKAHE020CT-ND
TP1: SWDIO; TestPoint_Pad_D1.0mm
TP2: SWDCLK; TestPoint_Pad_D1.0mm
U1: NEH7100; QFN40P400X400X90-29N-D; Mouser Part Number 771-NEH7100BUHP
X1: 32.768 kHz; Crystal_SMD_2012-2Pin_2.0x1.2mm; Part Number CM7V-T1A-LOW-ESR-32.768KHZ-9PF-20-TA-QC

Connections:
+5V: J2.A4 (VBUS), J2.A9 (VBUS), J2.B4 (VBUS), J2.B9 (VBUS), R1.2, R2.2, U1.11 (USB)
/CC1: J2.A5 (CC1), R1.1
/CC2: J2.B5 (CC2), R2.1
/CDC: CDC1.2, U1.3 (CDC)
/CMPPT: CMPPT1.2, U1.7 (CMPPT)
/DISABLE: JP9.2 (B), U1.10 (DISABLE)
/HC0: JP3.2 (C), U1.21 (HC0)
/HC1: JP4.2 (C), U1.20 (HC1)
/HC2: JP5.2 (C), U1.19 (HC2)
/HC3: JP6.2 (C), U1.18 (HC3)
/HC4: JP7.2 (C), U1.17 (HC4)
/P0.00: IC1.38 (P0.00), SW1.1
/P1.02/NFC1: IC1.11 (P1.02/NFC1), J4.1
/P1.03/NFC2/CLK: IC1.9 (P1.03/NFC2/CLK), J4.2
/P1.06: IC1.7 (P1.06), J4.3
/P1.13: IC1.20 (P1.13), J3.8
/P1.14: IC1.18 (P1.14), J3.7
/P1.15: IC1.16 (P1.15), J3.6
/P2.00: IC1.2 (P2.00), J3.4
/P2.01/CLK: IC1.6 (P2.01/CLK), J3.3
/P2.04: IC1.45 (P2.04), J3.2
/P2.05: IC1.1 (P2.05), J3.5
/P2.06/CLK: IC1.43 (P2.06/CLK), J3.1
/P2.08: D2.2 (A), IC1.26 (P2.08)
/SCL: IC1.3 (P1.08/EXTREF/CLK16M/CLK), J1.4, U1.16 (SCL)
/SCL1: IC1.17 (P1.04/AIN0/CLK)
/SCL2: IC1.29 (P0.04/CLK)
/SDA: IC1.8 (P1.07), J1.3, U1.15 (SDA)
/SDA1: IC1.15 (P1.05)
/SDA2: IC1.30 (P0.02)
/SWDCLK: IC1.25 (SWDCLK), J2.A3 (TX1-), TP2.1
/SWDIO: IC1.27 (SWDIO), J2.A2 (TX1+), TP1.1
/SWO: IC1.42 (P2.07), J2.B3 (TX2-)
/VBAT: J4.10, J5.2, U1.14 (VBAT)
/VBAT_OK: J4.7, JP8.1 (A), U1.9 (VBATOK)
/VBUS: J4.9
/VIN: CIN1.1, J4.8, U1.24 (VIN)
/VOUT_EN: J4.6, JP8.2 (B), U1.12 (LDOEN)
/VSTOR: CSTR1.1, JP3.1 (A), JP4.1 (A), JP5.3 (B), JP6.1 (A), JP7.1 (A), U1.22 (CSTORE)
/XL1: IC1.12 (P1.00/XL1), X1.2
/XL2: IC1.10 (P1.01/XL2), X1.1
/~RESET: IC1.32 (NRESET), J2.B2 (TX2+)
GND: CDC1.1, CIN1.2, CMPPT1.1, COUT1.2, CSTR1.2, IC1.4 (GND_1), IC1.14 (GND_2), IC1.24 (GND_3), IC1.28 (GND_4), IC1.31 (GND_5), IC1.34 (GND_6), IC1.36 (GND_7), IC1.39 (GND_8), IC1.46 (GND_9), IC1.47 (GND_10), IC1.48 (GND_11), IC1.49 (GND_12), IC1.50 (GND_13), IC1.51 (GND_14), J1.1, J1.MP, J2.A1 (GND), J2.A12 (GND), J2.B1 (GND), J2.B8 (SBU2), J2.B12 (GND), J2.S1 (SHIELD), J3.11, J4.11, J5.1, JP3.3 (B), JP4.3 (B), JP5.1 (A), JP6.3 (B), JP7.3 (B), JP9.1 (A), R4.2, SW1.2, U1.4 (GND), U1.29 (GND_2)
unnamed: D2.1 (K), R4.1
unnamed: CFLY1.2, U1.26 (CFLY1A)
unnamed: CFLY1.1, U1.25 (CFLY1B)
unnamed: CFLY2.2, U1.28 (CFLY2A)
unnamed: CFLY2.1, U1.27 (CFLY2B)
unnamed: CFLY3.2, U1.2 (CFLY3A)
unnamed: CFLY3.1, U1.1 (CFLY3B)
unnamed: CFLY4.2, U1.6 (CFLY4A)
unnamed: CFLY4.1, U1.5 (CFLY4B)
VDD: IC1.5 (VDD_NRF), J1.2, J2.A8 (SBU1), JP1.2 (B)
VLDO: COUT1.1, JP1.1 (A), U1.13 (VLDO)

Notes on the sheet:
I2C Address: 0x3C Inductorless energy harvesting PMIC Battery charger with OVP/LVP 15 μW to 100 mW input with MPTT USB charging up to 200 mA 200 mA LDO, 130 mV dropout Quiescent current 1.5 μA (2.1 with LDO)
I^{2}C Connector
USB-C Receptacle
Button
BL54L15μ (nrf54L15 module)
Test points
Pin Headers
Power and SWD Debugging
LED
NEH7100
Hard-coded settings Interpreted during power-up Connected to either "0" (GND) or "1" (VSTOR) May be overriden via I²C registers See section 7.3.7 in datasheet Default chosen for LFP/LiFePO4: 11011: OVP=3.5V LVD=2.5V LDO=Pass OCP=150mA Alternate to solder for NMC/etc: 00000: OVP=4.2V LVD=3.5V LDO=3.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
